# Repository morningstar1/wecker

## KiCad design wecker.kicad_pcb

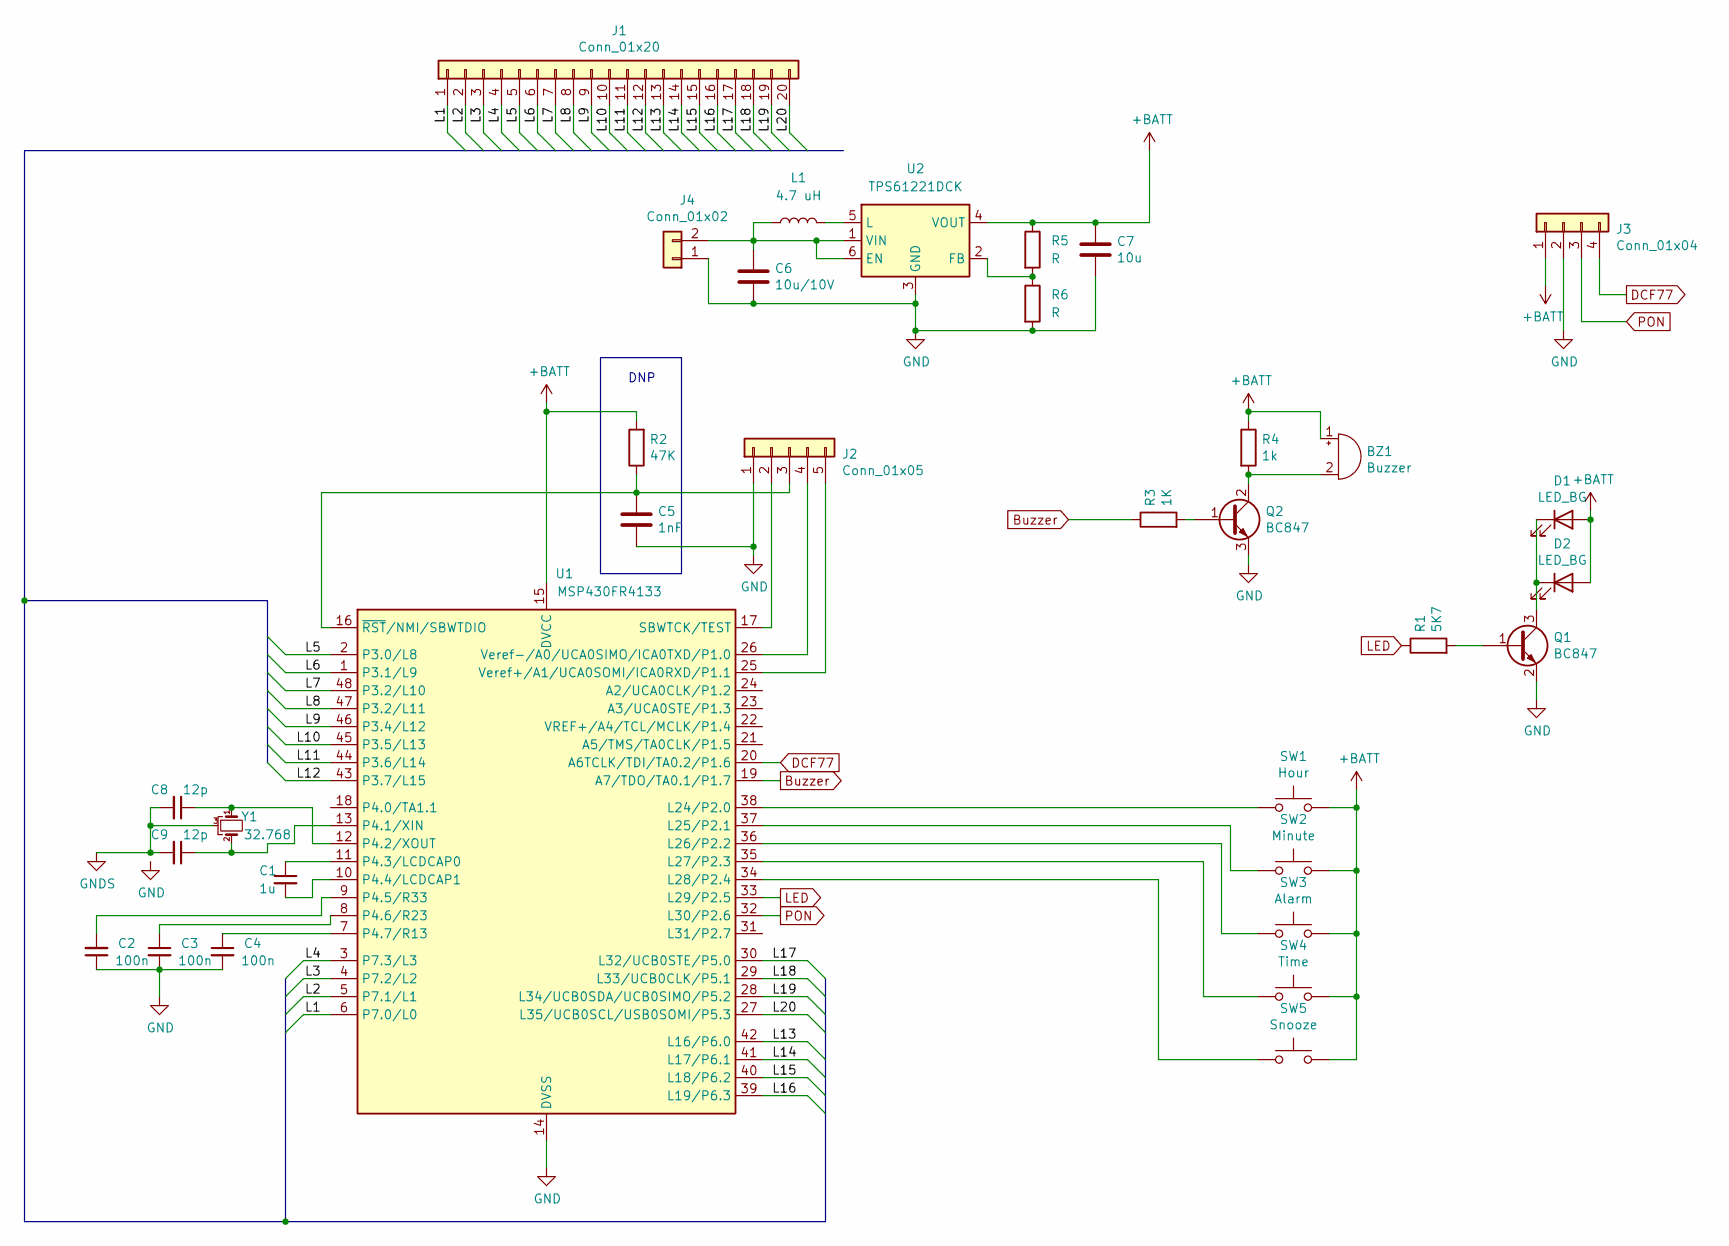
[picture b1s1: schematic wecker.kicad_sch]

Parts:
BZ1: Buzzer; Buzzer_TDK_PS1240P02BT_D12.2mm_H6.5mm
C1: 1u; C_0805_2012Metric_Pad1.15x1.40mm_HandSolder
C2, C3, C4: 100n; C_0805_2012Metric_Pad1.15x1.40mm_HandSolder
C5: 1nF; C_0805_2012Metric_Pad1.15x1.40mm_HandSolder
C6: 10u/10V; C_0805_2012Metric_Pad1.15x1.40mm_HandSolder
C7: 10u; C_0805_2012Metric_Pad1.15x1.40mm_HandSolder
C8, C9: 12p; C_0805_2012Metric_Pad1.15x1.40mm_HandSolder
D1, D2: LED_BG; LED_1210_3225Metric_Pad1.42x2.65mm_HandSolder
J1: Conn_01x20; LCD-20
J2: Conn_01x05; PinHeader_1x05_P2.54mm_Horizontal
J3: Conn_01x04; PinHeader_1x04_P2.54mm_Horizontal
J4: Conn_01x02; PinHeader_1x02_P2.54mm_Horizontal
L1: 4.7 uH; L_1206_3216Metric_Pad1.22x1.90mm_HandSolder
Q1, Q2: BC847; SOT-23
R1: 5K7; R_0805_2012Metric_Pad1.20x1.40mm_HandSolder
R2: 47K; R_0805_2012Metric_Pad1.20x1.40mm_HandSolder
R3: 1K; R_0805_2012Metric_Pad1.20x1.40mm_HandSolder
R4: 1k; R_0805_2012Metric_Pad1.20x1.40mm_HandSolder
R5, R6: R; R_0805_2012Metric_Pad1.20x1.40mm_HandSolder
SW1: Hour; SW_SPST_B3U-1000P
SW2: Minute; SW_SPST_B3U-1000P
SW3: Alarm; SW_SPST_B3U-1000P
SW4: Time; SW_SPST_B3U-1000P
SW5: Snooze; SW_SPST_B3U-1000P
U1: MSP430FR4133; TSSOP-48_6.1x12.5mm_P0.5mm
U2: TPS61221DCK; Texas_R-PDSO-G6
Y1: 32.768; Crystal_DS26_D2.0mm_L6.0mm_Horizontal_1EP_style1

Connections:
+BATT: BZ1.1 (-), C7.1, D1.2 (A), D2.2 (A), J3.1, R2.2, R4.1, R5.1, SW1.2, SW2.2, SW3.2, SW4.2, SW5.2, U1.15 (DVCC), U2.4 (VOUT)
/L1: J1.1, U1.6 (P7.0/L0)
/L2: J1.2, U1.5 (P7.1/L1)
/L3: J1.3, U1.4 (P7.2/L2)
/L4: J1.4, U1.3 (P7.3/L3)
/L5: J1.5, U1.2 (P3.0/L8)
/L6: J1.6, U1.1 (P3.1/L9)
/L7: J1.7, U1.48 (P3.2/L10)
/L8: J1.8, U1.47 (P3.2/L11)
/L9: J1.9, U1.46 (P3.4/L12)
/L10: J1.10, U1.45 (P3.5/L13)
/L11: J1.11, U1.44 (P3.6/L14)
/L12: J1.12, U1.43 (P3.7/L15)
/L13: J1.13, U1.42 (L16/P6.0)
/L14: J1.14, U1.41 (L17/P6.1)
/L15: J1.15, U1.40 (L18/P6.2)
/L16: J1.16, U1.39 (L19/P6.3)
/L17: J1.17, U1.30 (L32/UCB0STE/P5.0)
/L18: J1.18, U1.29 (L33/UCB0CLK/P5.1)
/L19: J1.19, U1.28 (L34/UCB0SDA/UCB0SIMO/P5.2)
/L20: J1.20, U1.27 (L35/UCB0SCL/USB0SOMI/P5.3)
Buzzer: R3.1, U1.19 (A7/TDO/TA0.1/P1.7)
DCF77: J3.4, U1.20 (A6TCLK/TDI/TA0.2/P1.6)
GND: C2.1, C3.2, C4.2, C5.1, C6.2, C7.2, J2.1, J3.2, J4.1, Q1.2 (E), Q2.3 (E), R6.2, U1.14 (DVSS), U2.3 (GND)
GNDS: C8.2, C9.2, Y1.3
LED: R1.1, U1.33 (L29/P2.5)
unnamed: BZ1.2 (+), Q2.2 (C), R4.2
unnamed: C1.1, U1.11 (P4.3/LCDCAP0)
unnamed: C1.2, U1.10 (P4.4/LCDCAP1)
unnamed: C2.2, U1.9 (P4.5/R33)
unnamed: C3.1, U1.8 (P4.6/R23)
unnamed: C4.1, U1.7 (P4.7/R13)
unnamed: C5.2, J2.3, R2.1, U1.16 (~RST/NMI/SBWTDIO)
unnamed: C6.1, J4.2, L1.1, U2.1 (VIN), U2.6 (EN)
unnamed: C8.1, U1.12 (P4.2/XOUT), Y1.1
unnamed: C9.1, U1.13 (P4.1/XIN), Y1.2
unnamed: D1.1 (K), D2.1 (K), Q1.3 (C)
unnamed: J2.2, U1.17 (SBWTCK/TEST)
unnamed: J2.4, U1.26 (Veref-/A0/UCA0SIMO/ICA0TXD/P1.0)
unnamed: J2.5, U1.25 (Veref+/A1/UCA0SOMI/ICA0RXD/P1.1)
unnamed: L1.2, U2.5 (L)
unnamed: Q1.1 (B), R1.2
unnamed: Q2.1 (B), R3.2
unnamed: R5.2, R6.1, U2.2 (FB)
unnamed: SW1.1, U1.38 (L24/P2.0)
unnamed: SW2.1, U1.37 (L25/P2.1)
unnamed: SW3.1, U1.36 (L26/P2.2)
unnamed: SW4.1, U1.35 (L27/P2.3)
unnamed: SW5.1, U1.34 (L28/P2.4)
PON: J3.3, U1.32 (L30/P2.6)

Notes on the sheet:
DNP

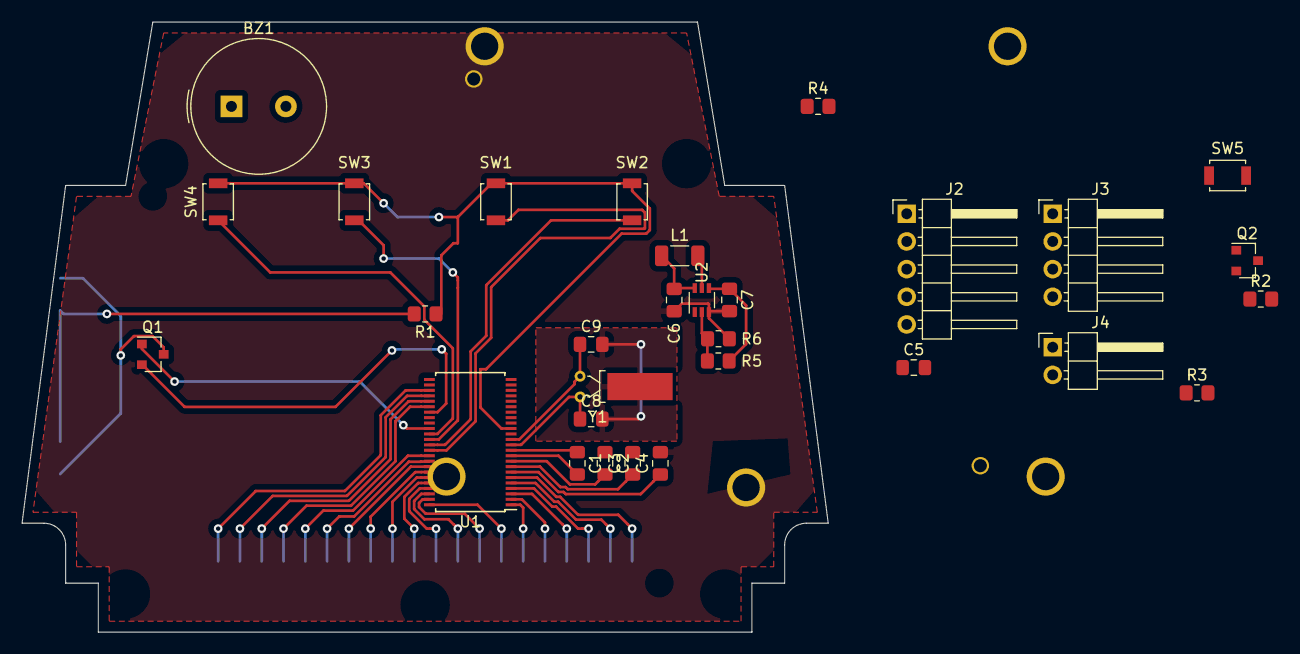
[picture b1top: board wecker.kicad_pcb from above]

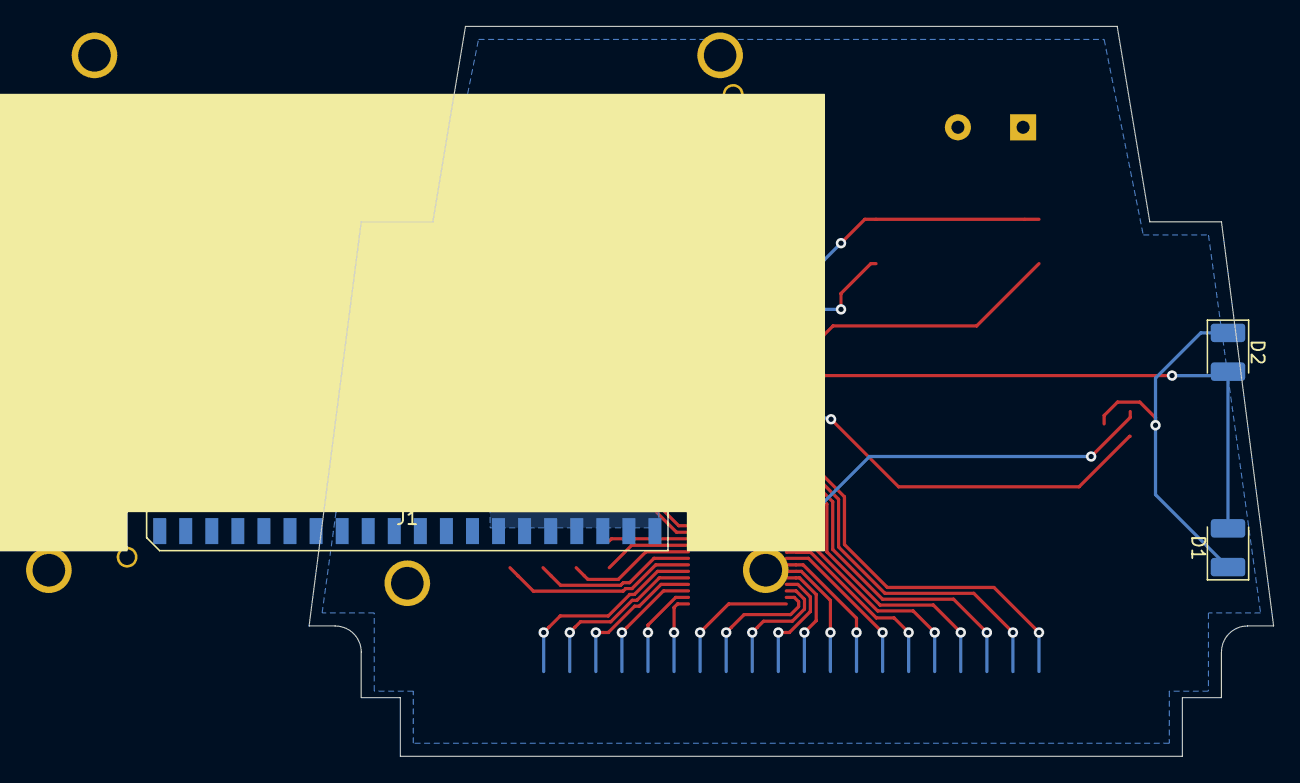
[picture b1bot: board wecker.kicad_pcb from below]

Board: 2 copper layers, 74.0 x 56.0 mm, 33 parts (3 on the bottom side), 50 nets.

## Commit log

2019-10-09 inital
2019-10-10 added some more parts
2019-10-10 exchange some parts
2019-10-10 correct PCB Measurements
2019-10-16 added Buzzer make LCD Bus
2019-11-01 still not ready
2019-11-14 some more corrections
2019-11-14 added docs
2019-11-17 set LED Rb and Tr Type
2022-07-16 Added TPS61221 Battery Chip
